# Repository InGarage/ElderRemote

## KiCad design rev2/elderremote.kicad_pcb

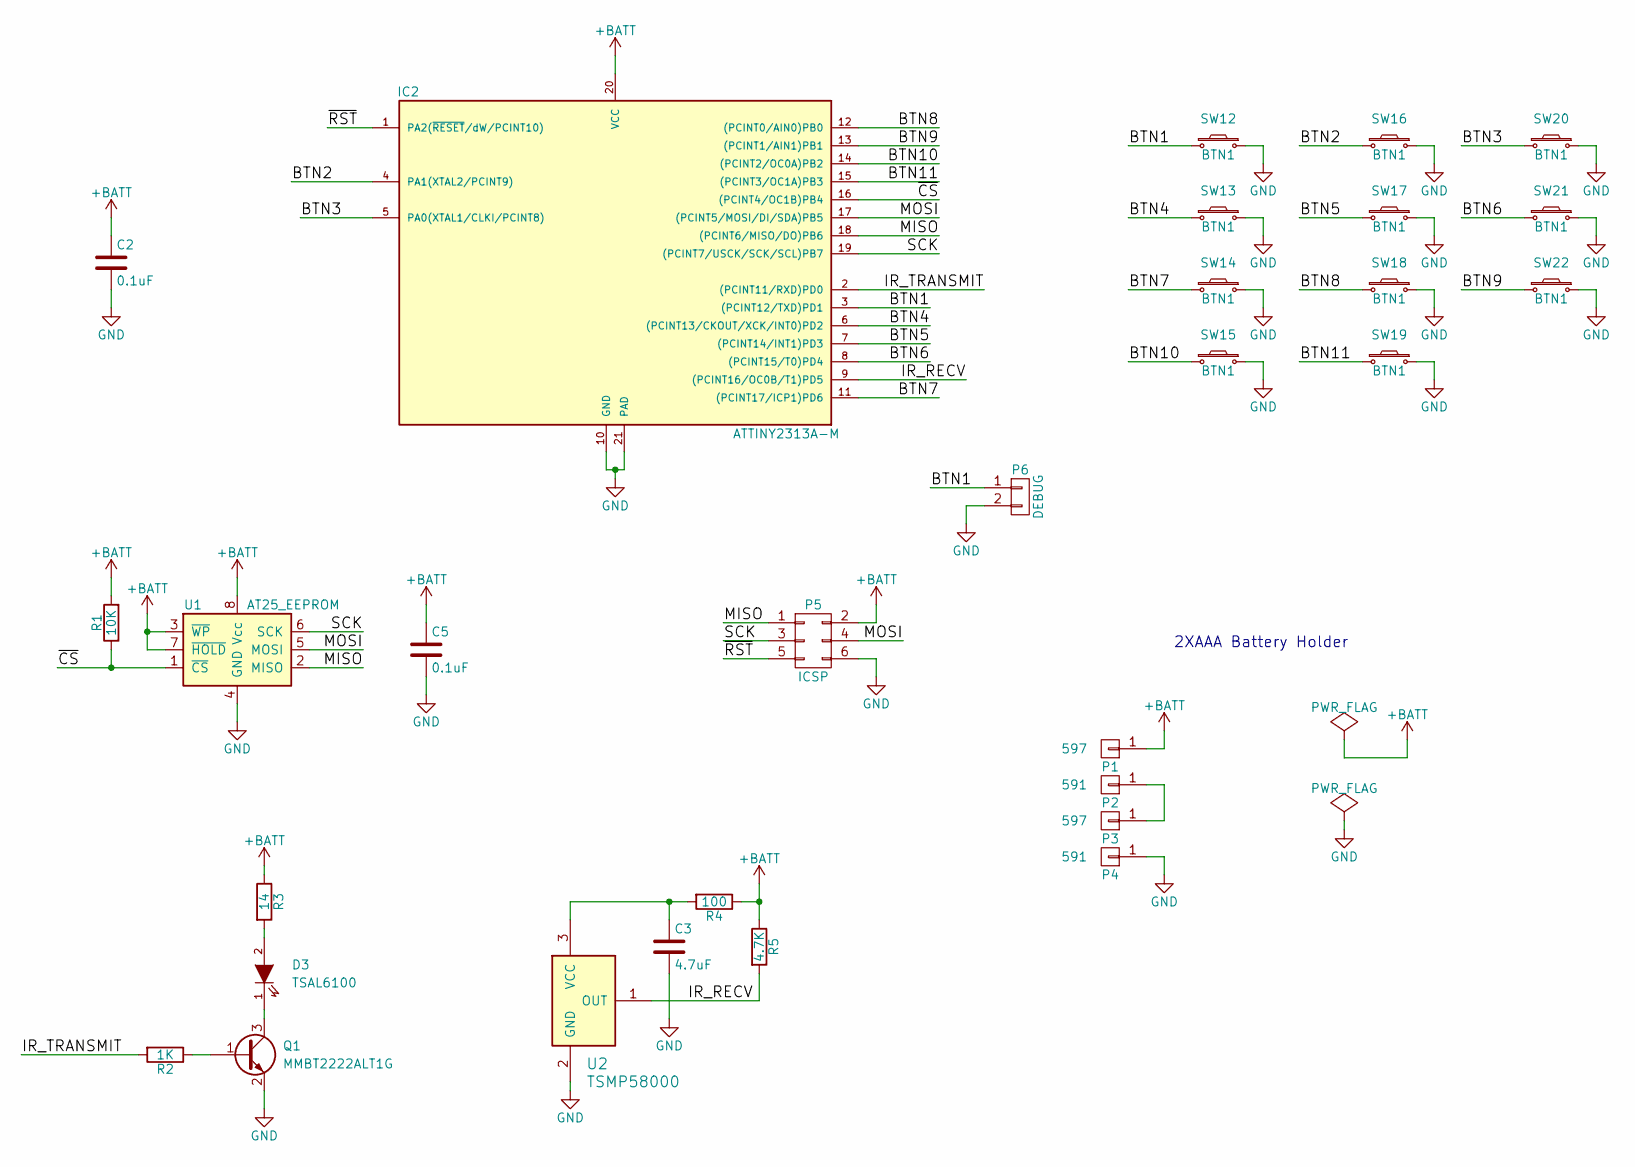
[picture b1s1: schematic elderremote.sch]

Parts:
C2, C5: 0.1uF; C_0805
C3: 4.7uF; C_0805
D3: TSAL6100; LED-5MM
IC2: ATTINY2313A-M; 20M1
P1, P3: 597
P2, P4: 591
P5: ICSP; Pin_Header_Straight_2x03
P6: DEBUG; Pin_Header_Straight_1x02
Q1: MMBT2222ALT1G; SOT-23
R1: 10K; R_0805
R2: 1K; R_0805
R3: 14; R_0805
R4: 100; R_0805
R5: 4.7K; R_0805
SW12, SW13, SW14, SW15, SW16, SW17, SW18, SW19, SW20, SW21, SW22: BTN1; SKPD
U1: AT25_EEPROM; SOIC-8_3.9x4.9mm_Pitch1.27mm
U2: TSMP58000

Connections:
+BATT: C2.1, C5.1, IC2.20 (VCC), P1.1, P5.2, R1.2, R3.1, R4.1, R5.1, U1.3 (~WP), U1.7 (~HOLD), U1.8 (Vcc)
/BTN1: IC2.3 ((PCINT12/TXD)PD1), P6.1, SW12.1
/BTN2: IC2.4 (PA1(XTAL2/PCINT9)), SW16.1
/BTN3: IC2.5 (PA0(XTAL1/CLKI/PCINT8)), SW20.1
/BTN4: IC2.6 ((PCINT13/CKOUT/XCK/INT0)PD2), SW13.1
/BTN5: IC2.7 ((PCINT14/INT1)PD3), SW17.1
/BTN6: IC2.8 ((PCINT15/T0)PD4), SW21.1
/BTN7: IC2.11 ((PCINT17/ICP1)PD6), SW14.1
/BTN8: IC2.12 ((PCINT0/AIN0)PB0), SW18.1
/BTN9: IC2.13 ((PCINT1/AIN1)PB1), SW22.1
/BTN10: IC2.14 ((PCINT2/OC0A)PB2), SW15.1
/BTN11: IC2.15 ((PCINT3/OC1A)PB3), SW19.1
/IR_RECV: IC2.9 ((PCINT16/OC0B/T1)PD5), R5.2, U2.1 (OUT)
/IR_TRANSMIT: IC2.2 ((PCINT11/RXD)PD0), R2.2
/MISO: IC2.18 ((PCINT6/MISO/DO)PB6), P5.1, U1.2 (MISO)
/MOSI: IC2.17 ((PCINT5/MOSI/DI/SDA)PB5), P5.4, U1.5 (MOSI)
/SCK: IC2.19 ((PCINT7/USCK/SCK/SCL)PB7), P5.3, U1.6 (SCK)
/~CS: IC2.16 ((PCINT4/OC1B)PB4), R1.1, U1.1 (~CS)
/~RST: IC2.1 (PA2(~RESET~/dW/PCINT10)), P5.5
GND: C2.2, C3.2, C5.2, IC2.10 (GND), IC2.21 (PAD), P4.1, P5.6, P6.2, Q1.2 (E), SW12.2, SW13.2, SW14.2, SW15.2, SW16.2, SW17.2, SW18.2, SW19.2, SW20.2, SW21.2, SW22.2, U1.4 (GND), U2.2 (GND)
unnamed: C3.1, R4.2, U2.3 (VCC)
unnamed: D3.1 (K), Q1.3 (C)
unnamed: D3.2 (A), R3.2
unnamed: P2.1, P3.1
unnamed: Q1.1 (B), R2.1

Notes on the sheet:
2XAAA Battery Holder

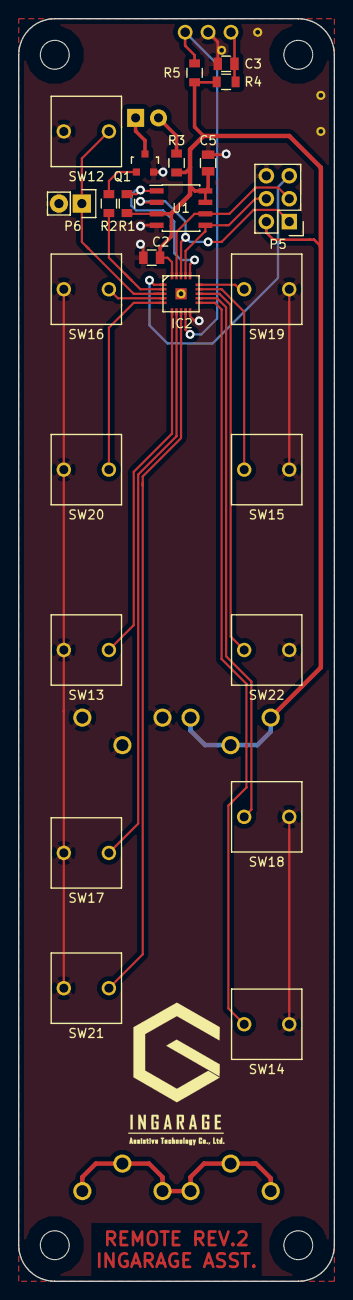
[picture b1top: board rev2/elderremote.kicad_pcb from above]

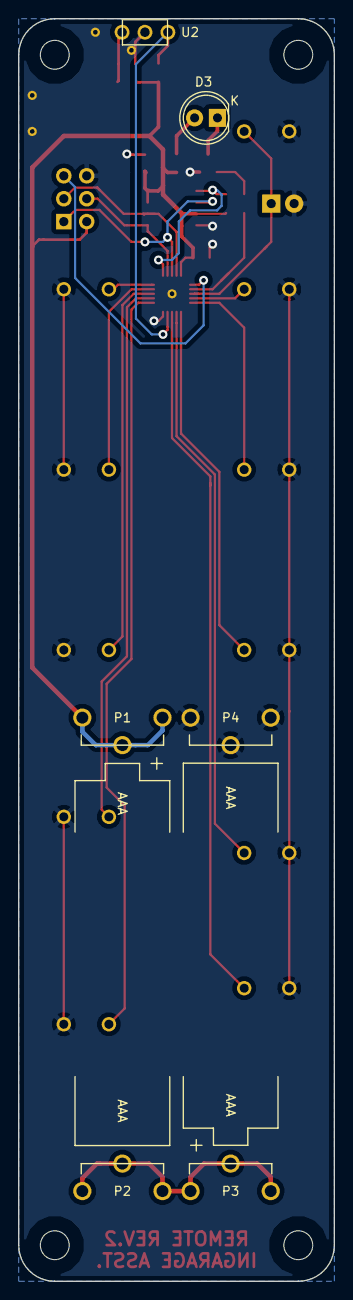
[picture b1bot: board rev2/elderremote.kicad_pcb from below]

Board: 2 copper layers, 35.0 x 140.0 mm, 30 parts (6 on the bottom side), 25 nets.

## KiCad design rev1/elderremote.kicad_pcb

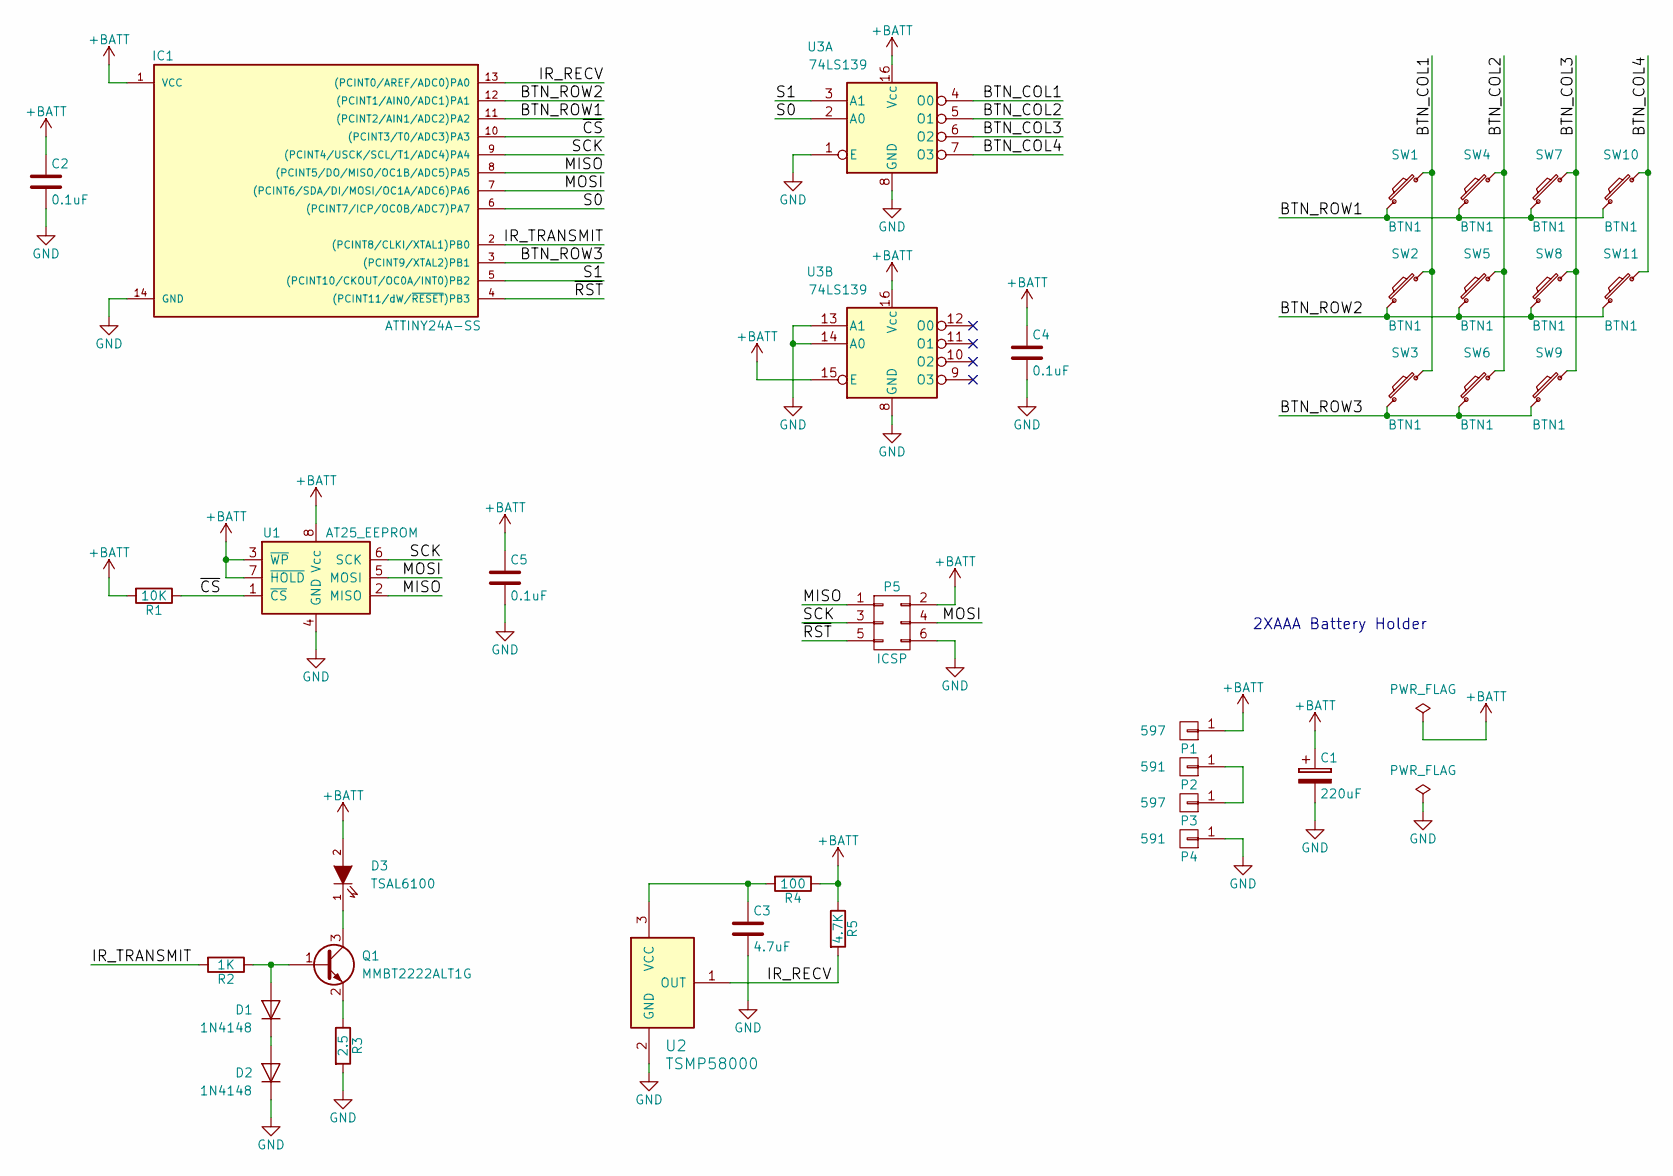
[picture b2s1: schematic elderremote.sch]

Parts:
C1: 220uF; TantalC_SizeB_EIA-3528_Reflow
C2, C4, C5: 0.1uF; C_0805
C3: 4.7uF; C_0805
D1, D2: 1N4148; SOD80
D3: TSAL6100; LED-5MM
IC1: ATTINY24A-SS; SOIC-14_3.9x8.7mm_Pitch1.27mm
P1, P3: 597
P2, P4: 591
P5: ICSP; Pin_Header_Straight_2x03
Q1: MMBT2222ALT1G; SOT-23
R1: 10K; R_0805
R2: 1K; R_0805
R3: 2.5; R_0805
R4: 100; R_0805
R5: 4.7K; R_0805
SW1, SW2, SW3, SW4, SW5, SW6, SW7, SW8, SW9, SW10, SW11: BTN1; EVPAS
U1: AT25_EEPROM; SOIC-8_3.9x4.9mm_Pitch1.27mm
U2: TSMP58000
U3: 74LS139; TSSOP-16_4.4x5mm_Pitch0.65mm

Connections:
+BATT: C1.1, C2.1, C4.1, C5.1, D3.2 (A), IC1.1 (VCC), P1.1, P5.2, R1.2, R4.1, R5.1, U1.3 (~WP), U1.7 (~HOLD), U1.8 (Vcc), U3.15 (E), U3.16 (Vcc)
/BTN_COL1: SW1.2, SW2.2, SW3.2, U3.4 (O0)
/BTN_COL2: SW4.2, SW5.2, SW6.2, U3.5 (O1)
/BTN_COL3: SW7.2, SW8.2, SW9.2, U3.6 (O2)
/BTN_COL4: SW10.2, SW11.2, U3.7 (O3)
/BTN_ROW1: IC1.11 ((PCINT2/AIN1/ADC2)PA2), SW1.1, SW4.1, SW7.1, SW10.1
/BTN_ROW2: IC1.12 ((PCINT1/AIN0/ADC1)PA1), SW2.1, SW5.1, SW8.1, SW11.1
/BTN_ROW3: IC1.3 ((PCINT9/XTAL2)PB1), SW3.1, SW6.1, SW9.1
/IR_RECV: IC1.13 ((PCINT0/AREF/ADC0)PA0), R5.2, U2.1 (OUT)
/IR_TRANSMIT: IC1.2 ((PCINT8/CLKI/XTAL1)PB0), R2.2
/MISO: IC1.8 ((PCINT5/DO/MISO/OC1B/ADC5)PA5), P5.1, U1.2 (MISO)
/MOSI: IC1.7 ((PCINT6/SDA/DI/MOSI/OC1A/ADC6)PA6), P5.4, U1.5 (MOSI)
/S0: IC1.6 ((PCINT7/ICP/OC0B/ADC7)PA7), U3.2 (A0)
/S1: IC1.5 ((PCINT10/CKOUT/OC0A/INT0)PB2), U3.3 (A1)
/SCK: IC1.9 ((PCINT4/USCK/SCL/T1/ADC4)PA4), P5.3, U1.6 (SCK)
/~CS~: IC1.10 ((PCINT3/T0/ADC3)PA3), R1.1, U1.1 (~CS)
/~RST~: IC1.4 ((PCINT11/dW/~RESET~)PB3), P5.5
GND: C1.2, C2.2, C3.2, C4.2, C5.2, D2.1 (K), IC1.14 (GND), P4.1, P5.6, R3.2, U1.4 (GND), U2.2 (GND), U3.1 (E), U3.8 (GND), U3.13 (A1), U3.14 (A0)
unnamed: C3.1, R4.2, U2.3 (VCC)
unnamed: D1.1 (K), D2.2 (A)
unnamed: D1.2 (A), Q1.1 (B), R2.1
unnamed: D3.1 (K), Q1.3 (C)
unnamed: P2.1, P3.1
unnamed: Q1.2 (E), R3.1

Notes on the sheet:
2XAAA Battery Holder

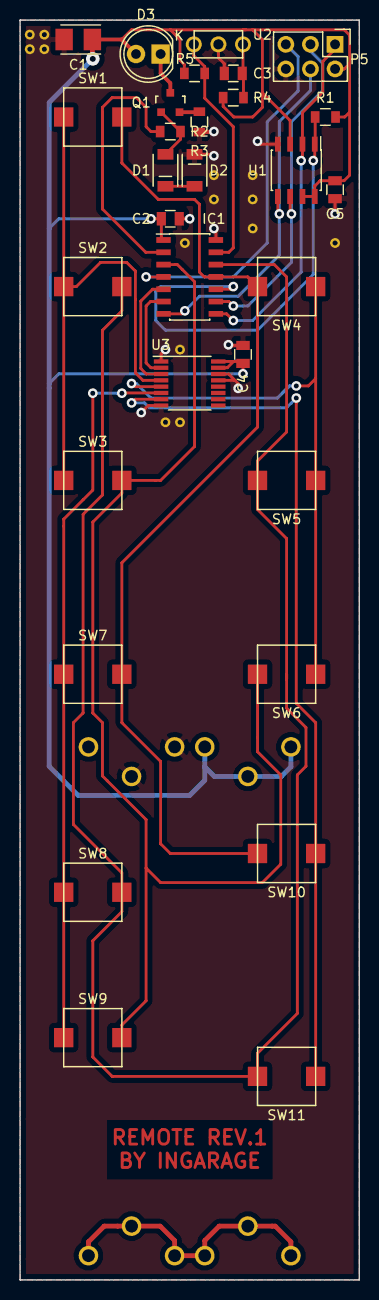
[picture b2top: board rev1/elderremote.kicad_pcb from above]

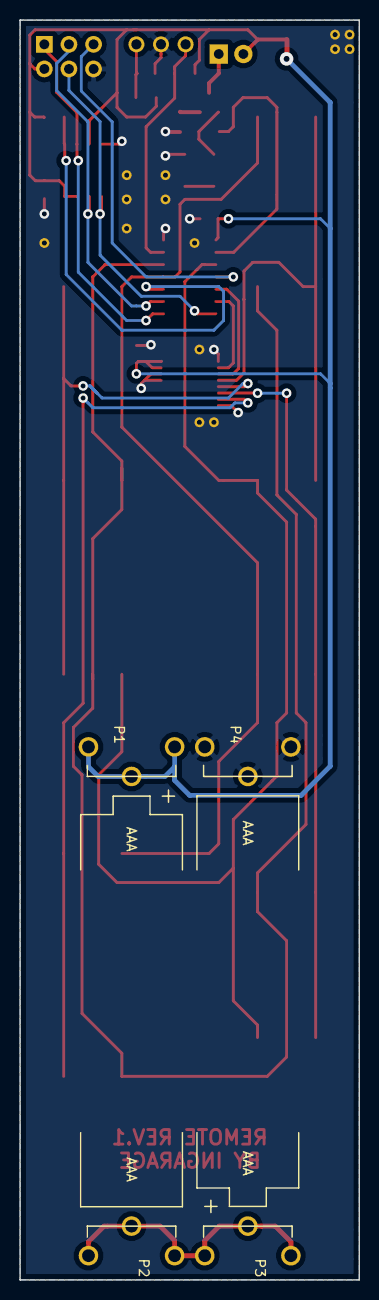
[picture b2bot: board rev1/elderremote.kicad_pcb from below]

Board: 2 copper layers, 35.0 x 130.0 mm, 34 parts (4 on the bottom side), 24 nets.
